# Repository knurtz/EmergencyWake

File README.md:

## Idea
A bedside alarm clock that uses a big red [emergency brake lever](https://www.google.com/search?tbm=isch&q=notbremse%20zug&tbs=imgo:1) as a snooze button.

To display the time, a vintage [VFD](https://en.wikipedia.org/wiki/Vacuum_fluorescent_display) is used.

An STM32 microcontroller and its RTC unit is used for tracking the time. It's in deep sleep most of the time.

Soundfiles from an SD card can be read by the microcontroller and played back through a small speaker.

Because of the VFD's relatively high power consumption, the clock can't run on battery power alone, so a USB-C connector is used for a 5 V power supply. 

In case of a power outage, a 3 V coin cell battery powers the microcontroller. In this scenario a small buzzer will be used instead of a wakeup melody, in order to use as little power as possible and to also notify the user, something's wrong. Also the display won't work.

Also, there will be support for a [DCF77](https://en.wikipedia.org/wiki/DCF77) radio clock module to automatically update the time.

A toggle switch allows programming two independent alarms. The times are set using a rotary encoder.

## Resources
- [Useful information](http://www.vwlowen.co.uk/arduino/vfd/vfd-clock.htm) about VFDs
- [A Guide to Fundamental VFD Operation](https://www.noritake-elec.com/technology/general-technical-information/vfd-operation)
- [Instructables page](https://www.instructables.com/id/A-Simple-Driver-for-VFD-Displays/) about controlling VFDs
- [Github project](https://github.com/AndruPol/ChibiOS-WavePlayer) about an STM32 wave player with ChibiOS
- [Github project](https://github.com/vanbwodonk/F4D_MP3) about an STM32 MP3 decoder
- [Another Github project](https://github.com/no111u3/stm32f4d_encoder/blob/master/main.c) about using the timer's encoder mode

## Components
- used emergency brake from eBay
- VFD from [pollin.de](https://www.pollin.de/p/vakuum-fluoreszenzdisplay-futaba-4-lt-46zb3-4-digit-121537) with additional parts:
  - [PT6312B](https://datasheet.lcsc.com/szlcsc/Princeton-Tech-PT6312B_C110225.pdf) VFD controller IC (requires negative voltages)
  - Alternative: UDN6118 VFD driver IC from eBay with no need for negative voltage
  - L9110 H-bridge for VFD filament
  - GL5516 light dependent resistor from eBay
- STM32F407VET6 microcontroller
- SD card holder from [Würth](https://www.we-online.de/katalog/datasheet/693071020811.pdf)
- DCF77 module from [pollin.de](https://www.pollin.de/p/dcf-empfangsmodul-dcf1-810054)
- CR2032 coin cell holder
- small buzzer
- toggle switch from [pollin.de](https://www.pollin.de/p/kippschalter-kn3-c-103a-1-polig-on-off-on-420023)
- rotary encoder from [reichelt.de](https://www.reichelt.de/drehimpulsegeber-15-impulse-30-rastungen-vertikal-stec11b03-p73913.html?r=1)
- MC34063 DCDC converter
- 5 V to 3.3 V step down regulator from [Würth](https://www.we-online.de/katalog/datasheet/173950378.pdf)
- [WM8960](https://datasheet.lcsc.com/szlcsc/Wolfson-Microelectronics-PLC-WM8960CGEFL-RV_C18752.pdf) audio codec with integrated class-D amplifier

## Usage
The clock will be in deep sleep most of the time. The display can be activated for about 10 seconds by tugging the emergency brake shortly.

While the time is being displayed, flipping the toggle switch into one of its two "on" positions allows setting the alarm times. In this mode, the alarms can each be (de-)activated by pulling the emergency lever once. A deactivated alarm will be represented by \_\_:\_\_ on the display.

Setting the alarm time is done by pressing the rotary encoder's push button to set the hours and then pressing it again to set the minutes. Alarm times are stored inside an EEPROM IC to avoid loss of settings after a power outage.

Once one alarm rings, pulling the emergency lever shortly will put it into snooze mode, pulling longer will deactivate the alarm.

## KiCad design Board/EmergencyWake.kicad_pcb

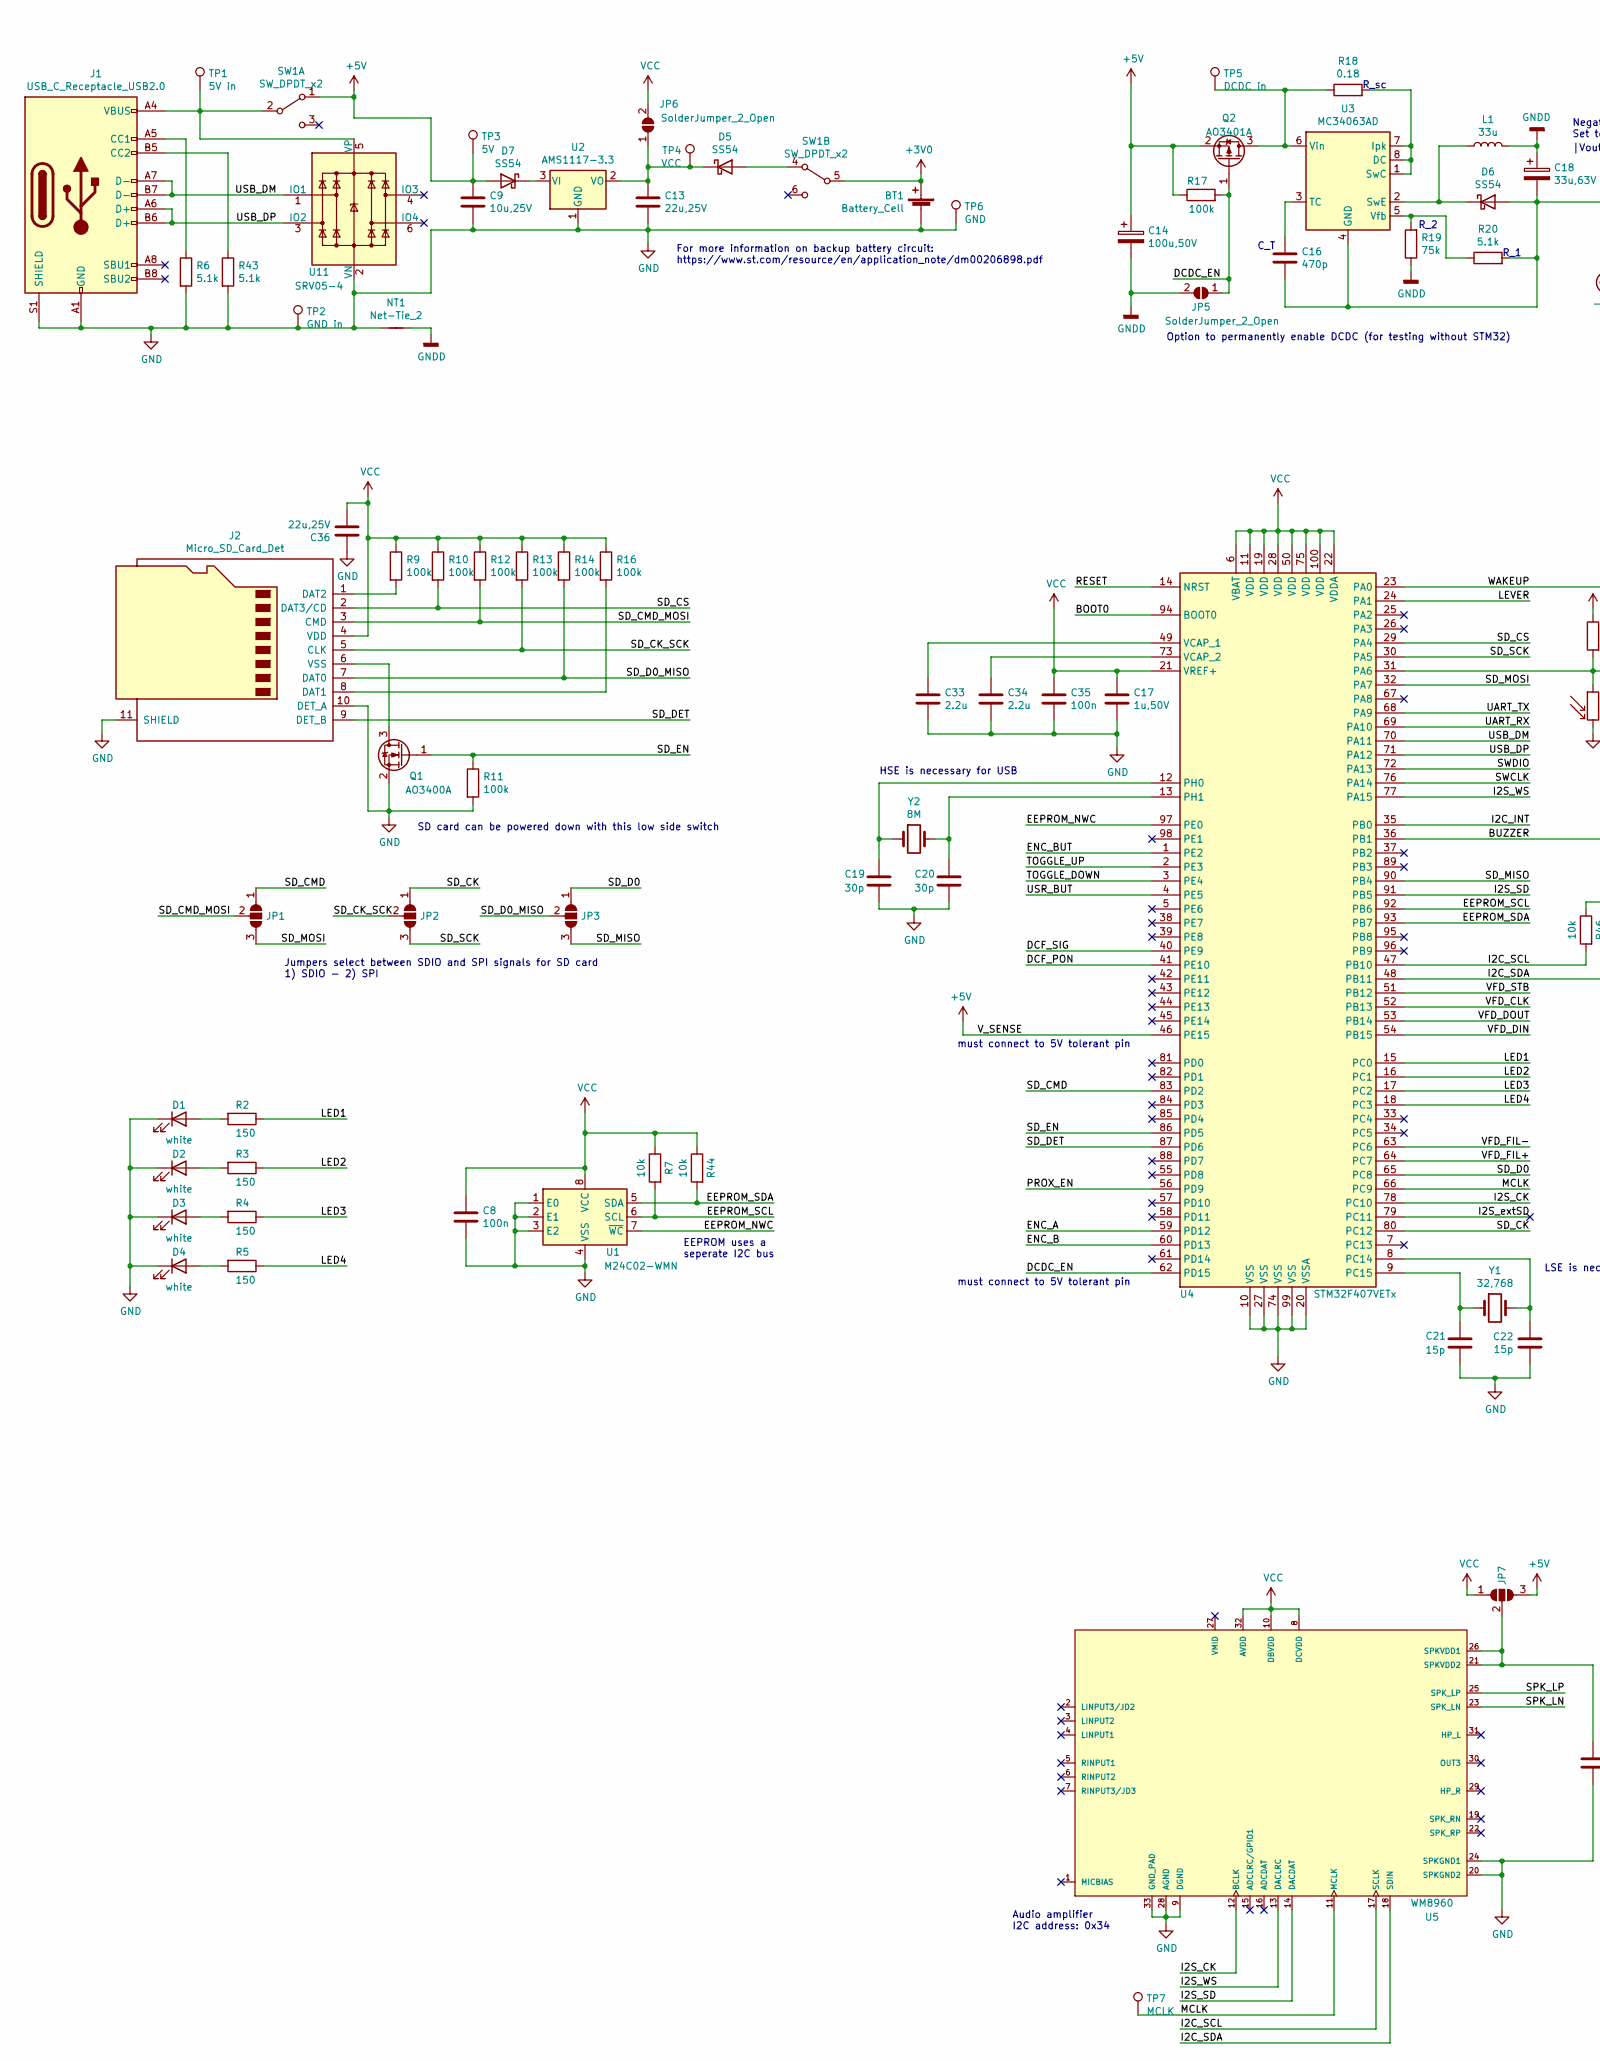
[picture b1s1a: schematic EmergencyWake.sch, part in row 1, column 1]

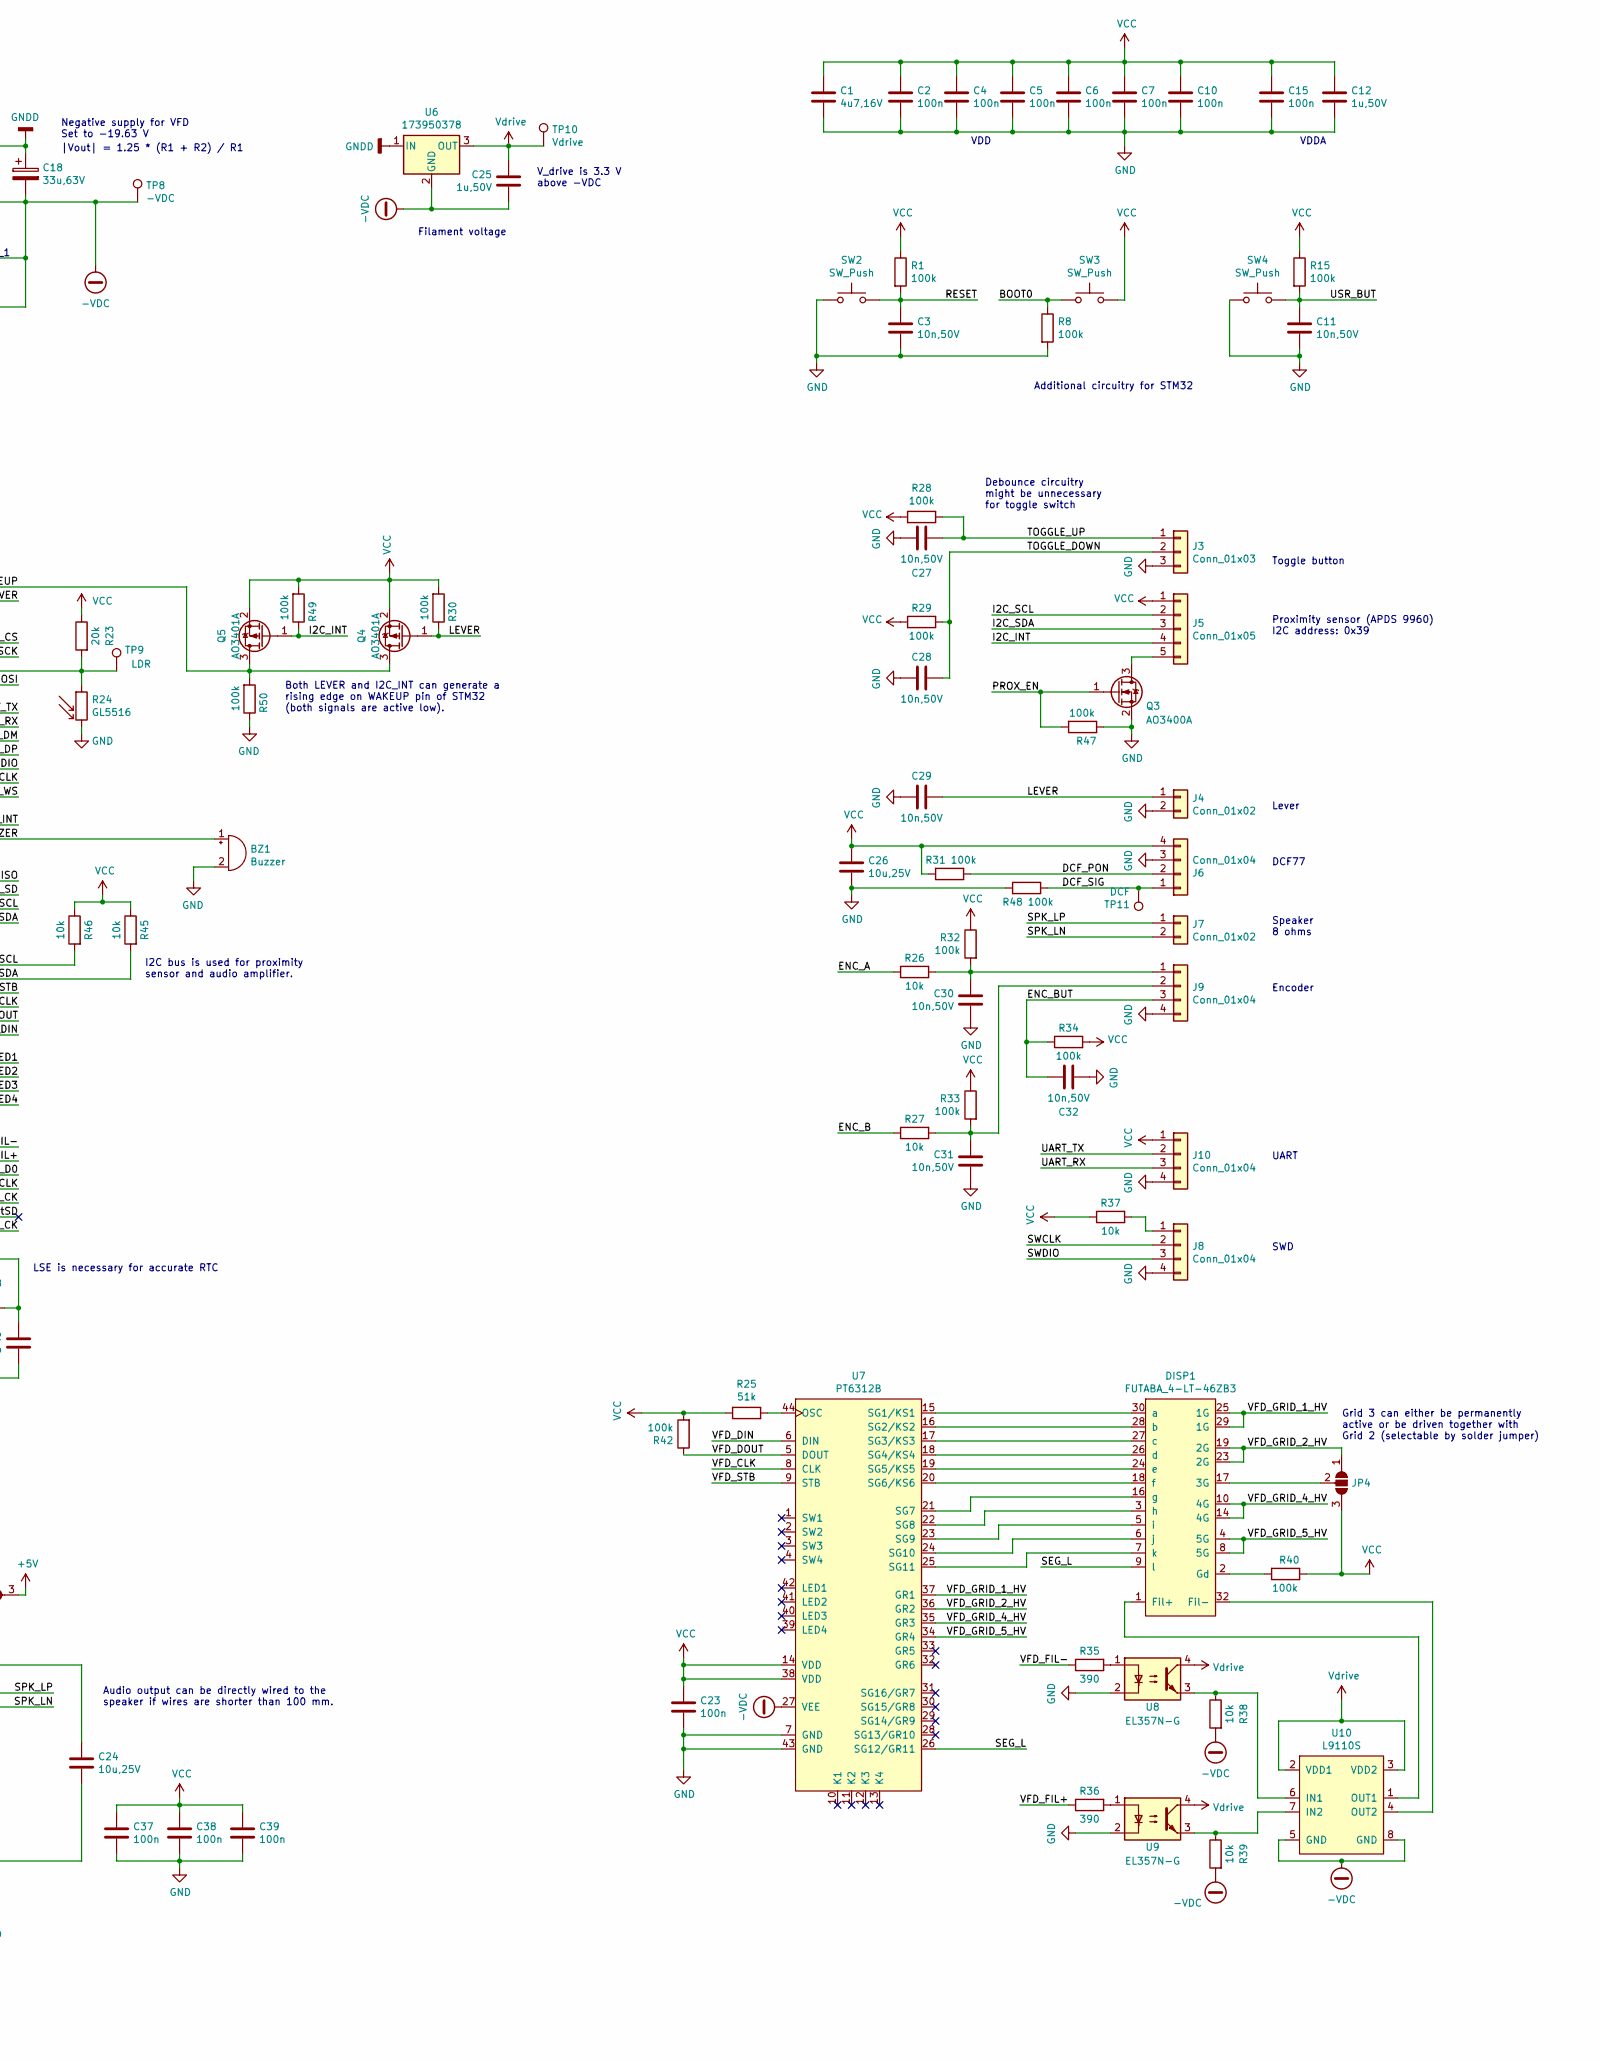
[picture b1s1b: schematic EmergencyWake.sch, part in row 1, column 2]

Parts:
BT1: Battery_Cell; 79523141
BZ1: Buzzer; Buzzer_12x9.5RM7.6
C1: 4u7,16V; C_0603_1608Metric; LCSC C19666
C2, C4, C5, C6, C7, C8, C10, C15, C23, C35, C37, C38, C39: 100n; C_0402_1005Metric; LCSC C1525
C3, C11, C27, C28, C29, C30, C31, C32: 10n,50V; C_0402_1005Metric; LCSC C15195
C9, C24, C26: 10u,25V; C_0805_2012Metric; LCSC C15850
C12, C17, C25: 1u,50V; C_0603_1608Metric; LCSC C15849
C13, C36: 22u,25V; C_0805_2012Metric; LCSC C45783
C14: 100u,50V; CP_Radial_D6.3mm_P2.50mm
C16: 470p; C_0603_1608Metric; LCSC C1620
C18: 33u,63V; CP_Radial_D6.3mm_P2.50mm
C19, C20: 30p; C_0402_1005Metric; LCSC C1570
C21, C22: 15p; C_0402_1005Metric; LCSC C1548
C33, C34: 2.2u; C_0603_1608Metric; LCSC C23630
D1, D2, D3, D4: white; LED_0805_2012Metric_Castellated; LCSC C34499
D5, D6, D7: SS54; D_SMA; LCSC C22452
DISP1: FUTABA_4-LT-46ZB3
J1: USB_C_Receptacle_USB2.0; 632723300011
J2: Micro_SD_Card_Det; 693071020811
J3: Conn_01x03; PinHeader_1x03_P2.54mm_Horizontal
J4, J7: Conn_01x02; PinHeader_1x02_P2.54mm_Horizontal
J5: Conn_01x05; PinHeader_1x05_P2.54mm_Horizontal
J6, J9: Conn_01x04; PinHeader_1x04_P2.54mm_Horizontal
J8, J10: Conn_01x04; WR-WTB 2.00mm SMT Male Horizontal Shrouded Header 4 Pins
JP1, JP2, JP3, JP4, JP7: SolderJumper_3_Open; SolderJumper-3_P1.3mm_Open_RoundedPad1.0x1.5mm_NumberLabels
JP5, JP6: SolderJumper_2_Open; SolderJumper-2_P1.3mm_Open_TrianglePad1.0x1.5mm
L1: 33u; L_Wuerth_WE-PD-Typ-7345
NT1: Net-Tie_2; NetTie-2_SMD_Pad2.0mm
Q1, Q3: AO3400A; SOT-23; LCSC C20917
Q2, Q4, Q5: AO3401A; SOT-23; LCSC C15127
R1, R8, R9, R10, R11, R12, R13, R14, R15, R16, R17, R28, R29, R30, R31, R32, R33, R34, R40, R42, R47, R48, R49, R50: 100k; R_0402_1005Metric; LCSC C25741
R2, R3, R4, R5: 150; R_0402_1005Metric; LCSC C25082
R6, R20, R43: 5.1k; R_0603_1608Metric; LCSC C23186
R7, R44, R45, R46: 10k; R_0402_1005Metric; LCSC C25804
R18: 0.18; 561070332057
R19: 75k; R_0603_1608Metric; LCSC C23242
R23: 20k; R_0603_1608Metric; LCSC C4184
R24: GL5516; R_LDR_5.1x4.3mm_P3.4mm_Vertical
R25: 51k; R_0603_1608Metric; LCSC C23196
R26, R27: 10k; R_0402_1005Metric; LCSC C25744
R35, R36: 390; R_0603_1608Metric; LCSC C23151
R37, R38, R39: 10k; R_0603_1608Metric; LCSC C25804
SW1: SW_DPDT_x2; 452404020202
SW2, SW3, SW4: SW_Push; 436351045816
TP1: 5V in; TestPoint_Loop_D1.80mm_Drill1.0mm_Beaded
TP2: GND in; TestPoint_Loop_D1.80mm_Drill1.0mm_Beaded
TP3: 5V; TestPoint_Loop_D1.80mm_Drill1.0mm_Beaded
TP4: VCC; TestPoint_Loop_D1.80mm_Drill1.0mm_Beaded
TP5: DCDC in; TestPoint_Loop_D1.80mm_Drill1.0mm_Beaded
TP6: GND; TestPoint_Loop_D1.80mm_Drill1.0mm_Beaded
TP7: MCLK; TestPoint_Loop_D1.80mm_Drill1.0mm_Beaded
TP8: -VDC; TestPoint_Loop_D1.80mm_Drill1.0mm_Beaded
TP9: LDR; TestPoint_Loop_D1.80mm_Drill1.0mm_Beaded
TP10: Vdrive; TestPoint_Loop_D1.80mm_Drill1.0mm_Beaded
TP11: DCF; TestPoint_Loop_D1.80mm_Drill1.0mm_Beaded
U1: M24C02-WMN; SOIC-8_3.9x4.9mm_P1.27mm; LCSC C7562
U2: AMS1117-3.3; SOT-223-3_TabPin2; LCSC C6186
U3: MC34063AD; SOIC-8_3.9x4.9mm_P1.27mm; LCSC C32078
U4: STM32F407VETx; LQFP-100_14x14mm_P0.5mm; LCSC C28730
U5: WM8960; QFN-32-1EP_5x5mm_P0.5mm_EP3.45x3.45mm; LCSC C18752
U6: 173950378; Converter_DCDC_RECOM_R-78B-2.0_THT
U7: PT6312B; LQFP-44_10x10mm_P0.8mm; LCSC C110225
U8, U9: EL357N-G; SOP-4_3.8x4.1mm_P2.54mm; LCSC C6649
U10: L9110S; SOP-8_3.76x4.96mm_P1.27mm; LCSC C85174
U11: SRV05-4; SOT-23-6; LCSC C85364
Y1: 32,768; Crystal_SMD_3215-2Pin_3.2x1.5mm; LCSC C32346
Y2: 8M; Crystal_SMD_5032-2Pin_5.0x3.2mm; LCSC C115962

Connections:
+3V0: BT1.1 (+), SW1.5 (B)
+5V: C9.1, C14.1, D7.2 (A), JP7.3 (B), Q2.2 (S), R17.1, SW1.1 (A), TP3.1, U4.46 (PE15)
-VDC: C16.2, C18.2, C25.2, D6.2 (A), R20.2, R38.2, R39.2, TP8.1, U3.4 (GND), U6.2 (GND), U7.27 (VEE), U10.5 (GND), U10.8 (GND)
/BOOT0: R8.1, SW3.1, U4.94 (BOOT0)
/BUZZER: BZ1.1 (-), U4.36 (PB1)
/DCDC_EN: JP5.1 (A), Q2.1 (G), R17.2, U4.62 (PD15)
/DCF_PON: J6.2, R31.1, U4.41 (PE10)
/DCF_SIG: J6.1, R48.1, TP11.1, U4.40 (PE9)
/EEPROM_NWC: U1.7 (~WC), U4.97 (PE0)
/EEPROM_SCL: R7.2, U1.6 (SCL), U4.92 (PB6)
/EEPROM_SDA: R44.2, U1.5 (SDA), U4.93 (PB7)
/ENC_A: R26.1, U4.59 (PD12)
/ENC_B: R27.1, U4.60 (PD13)
/ENC_BUT: C32.2, J9.3, R34.1, U4.1 (PE2)
/I2C_INT: J5.4, Q5.1 (G), R49.1, U4.35 (PB0)
/I2C_SCL: J5.2, R46.2, U4.47 (PB10), U5.17 (SCLK)
/I2C_SDA: J5.3, R45.2, U4.48 (PB11), U5.18 (SDIN)
/I2S_CK: U4.78 (PC10), U5.12 (BCLK)
/I2S_SD: U4.91 (PB5), U5.14 (DACDAT)
/I2S_WS: U4.77 (PA15), U5.13 (DACLRC)
/I2S_extSD: U4.79 (PC11)
/LED1: R2.1, U4.15 (PC0)
/LED2: R3.1, U4.16 (PC1)
/LED3: R4.1, U4.17 (PC2)
/LED4: R5.1, U4.18 (PC3)
/LEVER: C29.2, J4.1, Q4.1 (G), R30.1, U4.24 (PA1)
/MCLK: TP7.1, U4.66 (PC9), U5.11 (MCLK)
/PROX_EN: Q3.1 (G), R47.2, U4.56 (PD9)
/RESET: C3.1, R1.2, SW2.2, U4.14 (NRST)
/SD_CK: JP2.1 (A), U4.80 (PC12)
/SD_CK_SCK: J2.5 (CLK), JP2.2 (C), R13.2
/SD_CMD: JP1.1 (A), U4.83 (PD2)
/SD_CMD_MOSI: J2.3 (CMD), JP1.2 (C), R12.2
/SD_CS: J2.2 (DAT3/CD), R10.2, U4.29 (PA4)
/SD_D0: JP3.1 (A), U4.65 (PC8)
/SD_D0_MISO: J2.7 (DAT0), JP3.2 (C), R14.2
/SD_DET: J2.9 (DET_B), U4.87 (PD6)
/SD_EN: Q1.1 (G), R11.1, U4.86 (PD5)
/SD_MISO: JP3.3 (B), U4.90 (PB4)
/SD_MOSI: JP1.3 (B), U4.32 (PA7)
/SD_SCK: JP2.3 (B), U4.30 (PA5)
/SEG_L: DISP1.9 (l), U7.26 (SG12/GR11)
/SPK_LN: J7.2, U5.23 (SPK_LN)
/SPK_LP: J7.1, U5.25 (SPK_LP)
/SWCLK: J8.2, U4.76 (PA14)
/SWDIO: J8.3, U4.72 (PA13)
/TOGGLE_DOWN: C28.2, J3.2, R29.1, U4.3 (PE4)
/TOGGLE_UP: C27.2, J3.1, R28.1, U4.2 (PE3)
/UART_RX: J10.3, U4.69 (PA10)
/UART_TX: J10.2, U4.68 (PA9)
/USB_DM: J1.A7 (D-), J1.B7 (D-), U4.70 (PA11), U11.1 (IO1)
/USB_DP: J1.A6 (D+), J1.B6 (D+), U4.71 (PA12), U11.3 (IO2)
/USR_BUT: C11.1, R15.2, SW4.2, U4.4 (PE5)
/VFD_CLK: U4.52 (PB13), U7.8 (CLK)
/VFD_DIN: U4.54 (PB15), U7.6 (DIN)
/VFD_DOUT: R42.1, U4.53 (PB14), U7.5 (DOUT)
/VFD_FIL+: R36.1, U4.64 (PC7)
/VFD_FIL-: R35.1, U4.63 (PC6)
/VFD_GRID_1_HV: DISP1.25 (1G), DISP1.29 (1G), U7.37 (GR1)
/VFD_GRID_2_HV: DISP1.19 (2G), DISP1.23 (2G), JP4.1 (A), U7.36 (GR2)
/VFD_GRID_4_HV: DISP1.10 (4G), DISP1.14 (4G), U7.35 (GR3)
/VFD_GRID_5_HV: DISP1.4 (5G), DISP1.8 (5G), U7.34 (GR4)
/VFD_STB: U4.51 (PB12), U7.9 (STB)
/WAKEUP: Q4.3 (D), Q5.3 (D), R50.2, U4.23 (PA0)
GND: BT1.2 (-), BZ1.2 (+), C1.2, C2.2, C3.2, C4.2, C5.2, C6.2, C7.2, C8.2, C9.2, C10.2, C11.2, C12.2, C13.2, C15.2, C17.2, C19.2, C20.2, C21.2, C22.2, C23.2, C24.2, C26.2, C27.1, C28.1, C29.1, C30.2, C31.2, C32.1, C33.2, C34.2, C35.2, C36.1, C37.2, C38.2, C39.2, D1.1 (K), D2.1 (K), D3.1 (K), D4.1 (K), J1.A1 (GND), J1.A12 (GND), J1.B1 (GND), J1.B12 (GND), J1.S1 (SHIELD), J2.10 (DET_A), J2.11 (SHIELD), J3.3, J4.2, J6.3, J8.4, J9.4, J10.4, NT1.1, Q1.2 (S), Q3.2 (S), R6.2, R8.2, R11.2, R24.2, R43.2, R47.1, R48.2, R50.1, SW2.1, SW4.1, TP2.1, TP6.1, U1.1 (E0), U1.2 (E1), U1.3 (E2), U1.4 (VSS), U2.1 (GND), U4.10 (VSS), U4.20 (VSSA), U4.27 (VSS), U4.74 (VSS), U4.99 (VSS), U5.9 (DGND), U5.20 (SPKGND2), U5.24 (SPKGND1), U5.28 (AGND), U5.33 (GND_PAD), U7.7 (GND), U7.43 (GND), U8.2, U9.2, U11.2 (VN)
GNDD: C14.2, C18.1, JP5.2 (B), L1.2, NT1.2, R19.1, U6.1 (IN)
unnamed: C13.1, D5.1 (K), JP6.1 (A), TP4.1, U2.2 (VO)
unnamed: C16.1, U3.3 (TC)
unnamed: C19.1, U4.12 (PH0), Y2.1
unnamed: C20.1, U4.13 (PH1), Y2.2
unnamed: C21.1, U4.9 (PC15), Y1.1
unnamed: C22.1, U4.8 (PC14), Y1.2
unnamed: C24.1, JP7.2 (C), U5.21 (SPKVDD2), U5.26 (SPKVDD1)
unnamed: C30.1, J9.1, R26.2, R32.2
unnamed: C31.1, J9.2, R27.2, R33.2
unnamed: C33.1, U4.49 (VCAP_1)
unnamed: C34.1, U4.73 (VCAP_2)
unnamed: D1.2 (A), R2.2
unnamed: D2.2 (A), R3.2
unnamed: D3.2 (A), R4.2
unnamed: D4.2 (A), R5.2
unnamed: D5.2 (A), SW1.4 (A)
unnamed: D6.1 (K), L1.1, U3.2 (SwE)
unnamed: D7.1 (K), U2.3 (VI)
unnamed: DISP1.1 (Fil+), U10.1 (OUT1)
unnamed: DISP1.2 (Gd), R40.2
unnamed: DISP1.3 (h), U7.22 (SG8)
unnamed: DISP1.5 (i), U7.23 (SG9)
unnamed: DISP1.6 (j), U7.24 (SG10)
unnamed: DISP1.7 (k), U7.25 (SG11)
unnamed: DISP1.16 (g), U7.21 (SG7)
unnamed: DISP1.17 (3G), JP4.2 (C)
unnamed: DISP1.18 (f), U7.20 (SG6/KS6)
unnamed: DISP1.24 (e), U7.19 (SG5/KS5)
unnamed: DISP1.26 (d), U7.18 (SG4/KS4)
unnamed: DISP1.27 (c), U7.17 (SG3/KS3)
unnamed: DISP1.28 (b), U7.16 (SG2/KS2)
unnamed: DISP1.30 (a), U7.15 (SG1/KS1)
unnamed: DISP1.32 (Fil-), U10.4 (OUT2)
unnamed: J1.A4 (VBUS), J1.A9 (VBUS), J1.B4 (VBUS), J1.B9 (VBUS), SW1.2 (B), TP1.1, U11.5 (VP)
unnamed: J1.A5 (CC1), R6.1
unnamed: J1.B5 (CC2), R43.1
unnamed: J2.1 (DAT2), R9.2
unnamed: J2.6 (VSS), Q1.3 (D)
unnamed: J2.8 (DAT1), R16.2
unnamed: J5.5, Q3.3 (D)
unnamed: J8.1, R37.2
unnamed: Q2.3 (D), R18.1, TP5.1, U3.6 (Vin)
unnamed: R18.2, U3.1 (SwC), U3.7 (Ipk), U3.8 (DC)
unnamed: R19.2, R20.1, U3.5 (Vfb)
unnamed: R23.2, R24.1, TP9.1, U4.31 (PA6)
unnamed: R25.1, U7.44 (OSC)
unnamed: R35.2, U8.1
unnamed: R36.2, U9.1
unnamed: R38.1, U8.3, U10.6 (IN1)
unnamed: R39.1, U9.3, U10.7 (IN2)
VCC: C1.1, C2.1, C4.1, C5.1, C6.1, C7.1, C8.1, C10.1, C12.1, C15.1, C17.1, C23.1, C26.1, C35.1, C36.2, C37.1, C38.1, C39.1, J2.4 (VDD), J5.1, J6.4, J10.1, JP4.3 (B), JP6.2 (B), JP7.1 (A), Q4.2 (S), Q5.2 (S), R1.1, R7.1, R9.1, R10.1, R12.1, R13.1, R14.1, R15.1, R16.1, R23.1, R25.2, R28.2, R29.2, R30.2, R31.2, R32.1, R33.1, R34.2, R37.1, R40.1, R42.2, R44.1, R45.1, R46.1, R49.2, SW3.2, U1.8 (VCC), U4.6 (VBAT), U4.11 (VDD), U4.19 (VDD), U4.21 (VREF+), U4.22 (VDDA), U4.28 (VDD), U4.50 (VDD), U4.75 (VDD), U4.100 (VDD), U5.8 (DCVDD), U5.10 (DBVDD), U5.32 (AVDD), U7.14 (VDD), U7.38 (VDD)
Vdrive: C25.1, TP10.1, U6.3 (OUT), U8.4, U9.4, U10.2 (VDD1), U10.3 (VDD2)

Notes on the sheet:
SWD
Speaker 8 ohms
DCF77
Toggle button
Lever
Encoder
must connect to 5V tolerant pin
For more information on backup battery circuit: https://www.st.com/resource/en/application_note/dm00206898.pdf
Debounce circuitry might be unnecessary for toggle switch
Grid 3 can either be permanently active or be driven together with Grid 2 (selectable by solder jumper)
Negative supply for VFD Set to -19.63 V
R_1
C_T
R_sc
|Vout| = 1.25 * (R1 + R2) / R1
VDD
VDDA
R_2
V_drive is 3.3 V above -VDC
Proximity sensor (APDS 9960) I2C address: 0x39
UART
Both LEVER and I2C_INT can generate a rising edge on WAKEUP pin of STM32 (both signals are active low).
I2C bus is used for proximity sensor and audio amplifier.
HSE is necessary for USB
LSE is necessary for accurate RTC
EEPROM uses a seperate I2C bus
Jumpers select between SDIO and SPI signals for SD card 1) SDIO - 2) SPI
SD card can be powered down with this low side switch
Option to permanently enable DCDC (for testing without STM32)
Filament voltage
Additional circuitry for STM32
Audio amplifier I2C address: 0x34
Audio output can be directly wired to the speaker if wires are shorter than 100 mm.

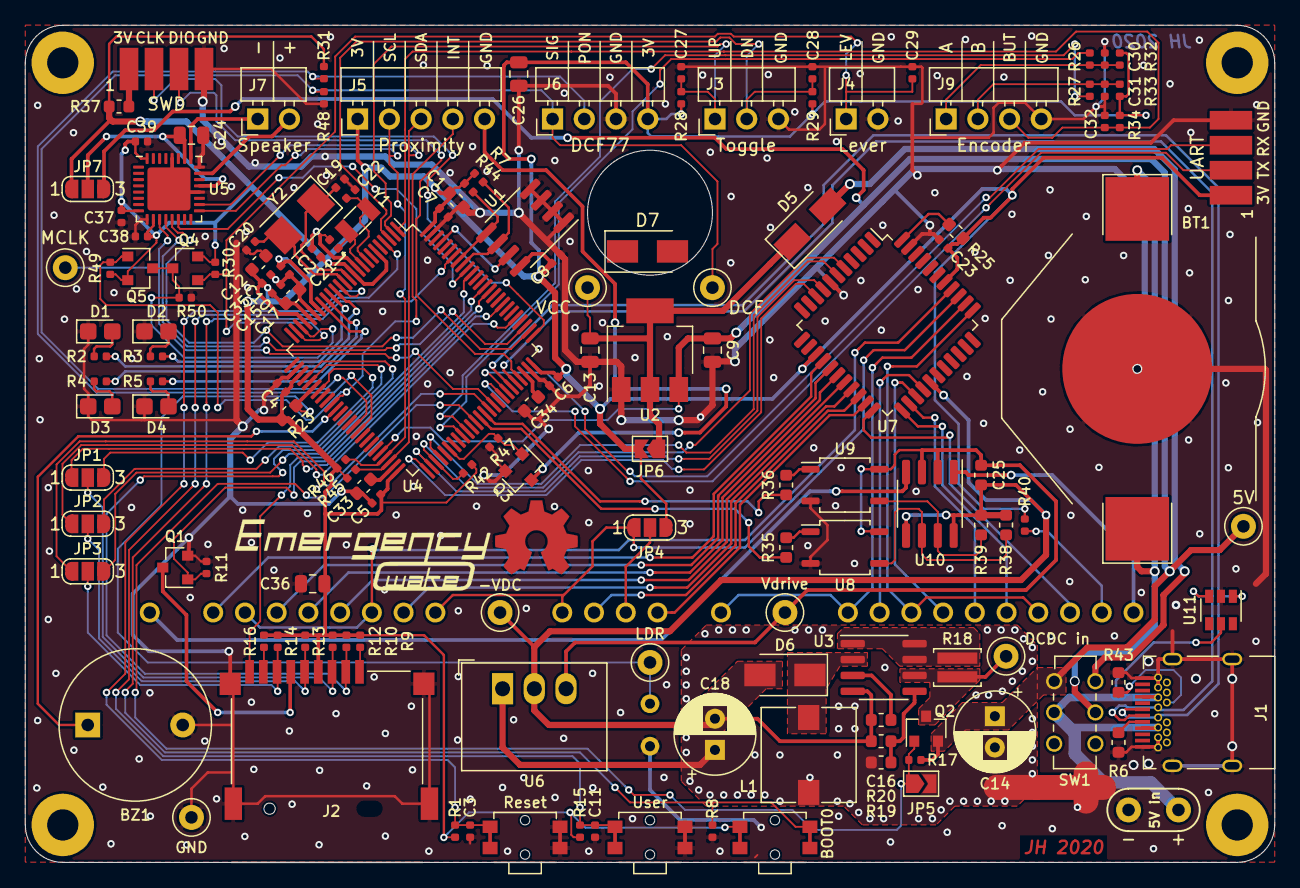
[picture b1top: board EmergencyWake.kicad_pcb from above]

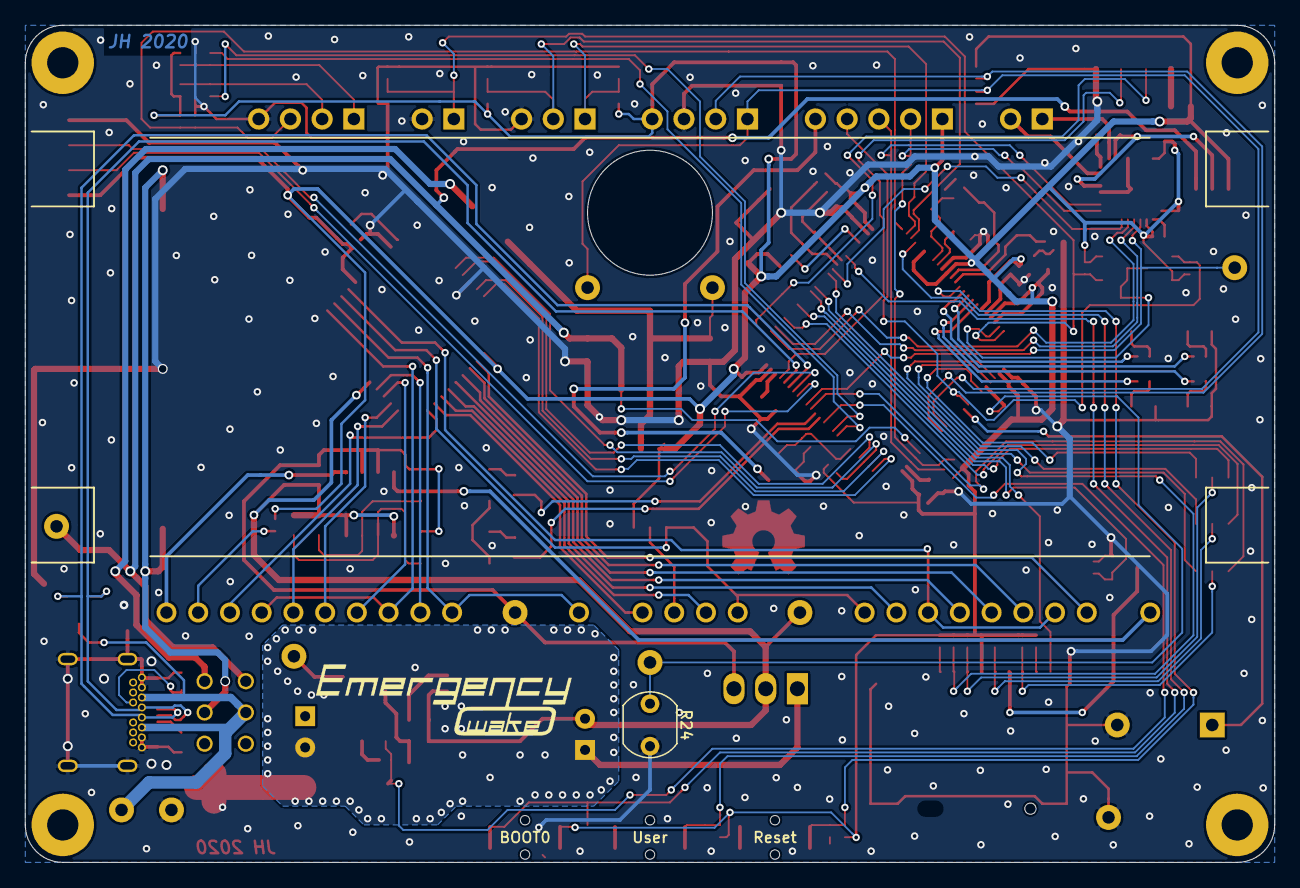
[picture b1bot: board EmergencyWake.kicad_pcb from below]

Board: 2 copper layers, 100.0 x 67.0 mm, 148 parts (2 on the bottom side), 117 nets.

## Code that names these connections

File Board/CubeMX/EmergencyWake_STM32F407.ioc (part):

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Mcu.Name=STM32F407V(E-G)Tx
Mcu.Package=LQFP100
Mcu.UserName=STM32F407VETx
PA0-WKUP.Mode=SYS_WakeUp0
PA0-WKUP.Signal=SYS_WKUP
PA1.GPIOParameters=GPIO_Label
PA1.GPIO_Label=Lever
PA1.Signal=GPXTI1
PA10.Mode=Asynchronous
PA10.Signal=USART1_RX
PA11.Mode=Device_Only
PA11.Signal=USB_OTG_FS_DM
PA12.Mode=Device_Only
PA12.Signal=USB_OTG_FS_DP
PA13.Mode=Serial_Wire
PA13.Signal=SYS_JTMS-SWDIO
PA14.Mode=Serial_Wire
PA14.Signal=SYS_JTCK-SWCLK
PA15.Mode=Full_Duplex_Master
PA15.Signal=I2S3_WS
PA4.Mode=NSS_Signal_Hard_Output
PA4.Signal=SPI1_NSS
PA5.Mode=Full_Duplex_Master
PA5.Signal=SPI1_SCK
PA6.GPIOParameters=GPIO_Label
PA6.GPIO_Label=LDR in
PA6.Signal=ADCx_IN6
PA7.Mode=Full_Duplex_Master
PA7.Signal=SPI1_MOSI
PA9.Mode=Asynchronous
PA9.Signal=USART1_TX
PB0.GPIOParameters=GPIO_Label
PB0.GPIO_Label=I2C_INT
PB0.Signal=GPXTI0
PB1.GPIOParameters=GPIO_Label
PB1.GPIO_Label=Buzzer
PB1.Signal=GPIO_Output
PB10.Mode=I2C
PB10.Signal=I2C2_SCL
PB11.Mode=I2C
PB11.Signal=I2C2_SDA
PB12.GPIOParameters=GPIO_Label
PB12.GPIO_Label=SPI2_STB
PB12.Signal=GPIO_Output
PB13.Mode=Full_Duplex_Master
PB13.Signal=SPI2_SCK
PB14.Mode=Full_Duplex_Master
PB14.Signal=SPI2_MISO
PB15.Mode=Full_Duplex_Master
PB15.Signal=SPI2_MOSI
PB4.Mode=Full_Duplex_Master
PB4.Signal=SPI1_MISO
PB5.Mode=Full_Duplex_Master
PB5.Signal=I2S3_SD
PB6.Mode=I2C
PB6.Signal=I2C1_SCL
PB7.Mode=I2C
PB7.Signal=I2C1_SDA
PC0.GPIOParameters=GPIO_Label
PC0.GPIO_Label=LED1
PC0.Signal=GPIO_Output
PC1.GPIOParameters=GPIO_Label
PC1.GPIO_Label=LED2
PC1.Signal=GPIO_Output
PC10.Mode=Full_Duplex_Master
PC10.Signal=I2S3_CK
PC11.Mode=Full_Duplex_Master
PC11.Signal=I2S3_ext_SD
PC12.Mode=SD_1_bit
PC12.Signal=SDIO_CK
PC14-OSC32_IN.Mode=LSE-External-Oscillator
PC14-OSC32_IN.Signal=RCC_OSC32_IN
PC15-OSC32_OUT.Mode=LSE-External-Oscillator
PC15-OSC32_OUT.Signal=RCC_OSC32_OUT
PC2.GPIOParameters=GPIO_Label
PC2.GPIO_Label=LED3
PC2.Signal=GPIO_Output
PC3.GPIOParameters=GPIO_Label
PC3.GPIO_Label=LED4
PC3.Signal=GPIO_Output
PC6.Signal=S_TIM8_CH1
PC7.Signal=S_TIM8_CH2
PC8.Mode=SD_1_bit
PC8.Signal=SDIO_D0
PC9.Mode=Clock-out-2
PC9.Signal=RCC_MCO_2
PD12.Signal=S_TIM4_CH1
PD13.Signal=S_TIM4_CH2
PD15.GPIOParameters=GPIO_Label
PD15.GPIO_Label=DCDC enable
PD15.Signal=GPIO_Output
PD2.Mode=SD_1_bit
PD2.Signal=SDIO_CMD
PD5.GPIOParameters=GPIO_Label
PD5.GPIO_Label=SD enable
PD5.Signal=GPIO_Output
PD6.GPIOParameters=GPIO_Label
PD6.GPIO_Label=SD detect
PD6.Signal=GPIO_Input
PD9.GPIOParameters=GPIO_Label
PD9.GPIO_Label=I2C2_EN
PD9.Signal=GPIO_Output
PE0.GPIOParameters=GPIO_Label
PE0.GPIO_Label=EEPROM_NWC
PE0.Signal=GPIO_Output
PE10.GPIOParameters=GPIO_Label
PE10.GPIO_Label=DCF77 enable
PE10.Signal=GPIO_Output
PE15.GPIOParameters=GPIO_Label
PE15.GPIO_Label=VBUS sense
PE15.Signal=GPIO_Input
PE2.GPIOParameters=GPIO_Label
PE2.GPIO_Label=EncoderButton
PE2.Signal=GPXTI2
PE3.GPIOParameters=GPIO_Label
PE3.GPIO_Label=ToggleUp
PE3.Signal=GPXTI3
PE4.GPIOParameters=GPIO_Label
PE4.GPIO_Label=ToggleDown
PE4.Signal=GPXTI4
PE5.GPIOParameters=GPIO_Label
PE5.GPIO_Label=USR_BUT
PE5.Signal=GPXTI5
PE9.GPIOParameters=GPIO_Label
PE9.GPIO_Label=DCF77 signal
PE9.Signal=S_TIM1_CH1
PH0-OSC_IN.Mode=HSE-External-Oscillator
PH0-OSC_IN.Signal=RCC_OSC_IN
PH1-OSC_OUT.Mode=HSE-External-Oscillator
PH1-OSC_OUT.Signal=RCC_OSC_OUT
RCC.HSE_VALUE=8000000
RCC.SYSCLKFreq_VALUE=72000000
RCC.SYSCLKSource=RCC_SYSCLKSOURCE_PLLCLK
board=custom

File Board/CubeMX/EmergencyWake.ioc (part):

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Mcu.Name=STM32F103V(C-D-E)Tx
Mcu.Package=LQFP100
Mcu.UserName=STM32F103VETx
PA0-WKUP.Mode=SYS_WakeUp0
PA0-WKUP.Signal=SYS_WKUP
PA1.GPIOParameters=GPIO_Label
PA1.GPIO_Label=Lever
PA1.Signal=GPXTI1
PA10.Mode=Asynchronous
PA10.Signal=USART1_RX
PA11.Mode=Device
PA11.Signal=USB_DM
PA12.Mode=Device
PA12.Signal=USB_DP
PA13.Mode=Serial_Wire
PA13.Signal=SYS_JTMS-SWDIO
PA14.Mode=Serial_Wire
PA14.Signal=SYS_JTCK-SWCLK
PA15.Mode=NSS_Signal_Hard_Input
PA15.Signal=SPI1_NSS
PA3.GPIOParameters=GPIO_Label
PA3.GPIO_Label=Audio EN
PA3.Signal=GPIO_Output
PA4.GPIOParameters=GPIO_Label
PA4.GPIO_Label=Audio out
PA4.Signal=COMP_DAC1_group
PA6.GPIOParameters=GPIO_Label
PA6.GPIO_Label=LDR in
PA6.Signal=ADCx_IN6
PA9.Mode=Asynchronous
PA9.Signal=USART1_TX
PB1.GPIOParameters=GPIO_Label
PB1.GPIO_Label=Buzzer
PB1.Signal=GPIO_Output
PB12.GPIOParameters=GPIO_Label
PB12.GPIO_Label=SPI2_STB
PB12.Signal=GPIO_Output
PB13.Mode=Full_Duplex_Master
PB13.Signal=SPI2_SCK
PB14.Mode=Full_Duplex_Master
PB14.Signal=SPI2_MISO
PB15.Mode=Full_Duplex_Master
PB15.Signal=SPI2_MOSI
PB3.Mode=Full_Duplex_Master
PB3.Signal=SPI1_SCK
PB4.Mode=Full_Duplex_Master
PB4.Signal=SPI1_MISO
PB5.Mode=Full_Duplex_Master
PB5.Signal=SPI1_MOSI
PB6.Mode=I2C
PB6.Signal=I2C1_SCL
PB7.Mode=I2C
PB7.Signal=I2C1_SDA
PC0.GPIOParameters=GPIO_Label
PC0.GPIO_Label=LED1
PC0.Signal=GPIO_Output
PC1.GPIOParameters=GPIO_Label
PC1.GPIO_Label=LED2
PC1.Signal=GPIO_Output
PC12.Mode=SD_1_bit
PC12.Signal=SDIO_CK
PC14-OSC32_IN.Mode=LSE-External-Oscillator
PC14-OSC32_IN.Signal=RCC_OSC32_IN
PC15-OSC32_OUT.Mode=LSE-External-Oscillator
PC15-OSC32_OUT.Signal=RCC_OSC32_OUT
PC2.GPIOParameters=GPIO_Label
PC2.GPIO_Label=LED3
PC2.Signal=GPIO_Output
PC3.GPIOParameters=GPIO_Label
PC3.GPIO_Label=LED4
PC3.Signal=GPIO_Output
PC6.Signal=S_TIM8_CH1
PC7.Signal=S_TIM8_CH2
PC8.Mode=SD_1_bit
PC8.Signal=SDIO_D0
PD12.Signal=S_TIM4_CH1
PD13.Signal=S_TIM4_CH2
PD15.GPIOParameters=GPIO_Label
PD15.GPIO_Label=DCDC enable
PD15.Signal=GPIO_Output
PD2.Mode=SD_1_bit
PD2.Signal=SDIO_CMD
PD5.GPIOParameters=GPIO_Label
PD5.GPIO_Label=SD enable
PD5.Signal=GPIO_Output
PD6.GPIOParameters=GPIO_Label
PD6.GPIO_Label=SD detect
PD6.Signal=GPIO_Input
PE0.GPIOParameters=GPIO_Label
PE0.GPIO_Label=EEPROM_NWC
PE0.Signal=GPIO_Output
PE10.GPIOParameters=GPIO_Label
PE10.GPIO_Label=DCF77 enable
PE10.Signal=GPIO_Output
PE15.GPIOParameters=GPIO_Label
PE15.GPIO_Label=VBUS sense
PE15.Signal=GPIO_Input
PE2.GPIOParameters=GPIO_Label
PE2.GPIO_Label=EncoderButton
PE2.Signal=GPXTI2
PE3.GPIOParameters=GPIO_Label
PE3.GPIO_Label=ToggleUp
PE3.Signal=GPXTI3
PE4.GPIOParameters=GPIO_Label
PE4.GPIO_Label=ToggleDown
PE4.Signal=GPXTI4
PE5.GPIOParameters=GPIO_Label
PE5.GPIO_Label=USR_BUT
PE5.Signal=GPXTI5
PE9.GPIOParameters=GPIO_Label
PE9.GPIO_Label=DCF77 signal
PE9.Signal=S_TIM1_CH1
board=custom

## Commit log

2020-01-19 [Initial commit] Folder strucure, Datasheet, CubeMX files
2020-01-19 [Board] Renamed CubeMX file
2020-01-19 Added readme
2020-01-19 Fixed typos in readme
2020-01-20 Link to DCF77
2020-01-20 [Readme] New toggle switch, link to encoder, typos
2020-01-20 [Readme] Link to timer in encoder mode
2020-01-21 [Readme] Added guide to VFD operation
2020-01-21 [Readme] Changed for new VFD IC with more features
2020-01-21 [Readme] Added instructables
2020-01-23 [Readme] Changed driver IC once again
2020-01-23 [Board] Started layout with mechanically fixed components
2020-01-23 [Board] Added a lot of main components
2020-01-24 [Board] Added a lot more components to schematic
2020-01-24 [Documents] Added STM32 datasheet, added PDF extension for manual
2020-01-25 [Board] Added IC and wiring for VFD
2020-01-25 [Documents] Added datasheet for VFD IC UDN6118
2020-01-25 [Board] Added motor driver for VFD filament
2020-01-27 [Board] Added all remaining components, arranged them approximately on PCB
2020-01-29 [Board] Switched some pins in CubeMX
2020-01-31 [Board] Changed VFD driver, added DC/DC converter for -24V
2020-02-01 [Board] Some tweaks on the schematic
2020-02-01 [Board] Wired all signals to STM32
2020-02-01 [Board] Cleaned up schematic sections
2020-02-02 [Board] Switched some pins around
2020-02-02 [Board] Placed a lot of components!
2020-02-03 [Board] Placed most components, only TPs missing
2020-02-05 [Board] Changed lever to active high, replaced LDO for filament
2020-02-05 [Board] Moved all components to the front of the board
2020-02-05 [Board] Finished moving components to front of board
2020-02-06 [Board] Checked schematic for errors
2020-02-09 [Images] Added Emergency Wake Logo
2020-02-09 [Board] Added logo and changed USB plug type
2020-02-09 [Board] Added GNDD and routed DCDC converter
2020-02-10 [Readme] Added logo
2020-02-10 [Readme] Documented recent changes in the design.
2020-02-10 [Board] Rearranged DCDC converter
2020-02-11 [Board] Cleaned up silkscreen
2020-02-12 [Libs] New footprints and 3D models for Würth components
2020-02-12 [Board] Changed SD and battery holder to Würth components
2020-02-12 [Board] Cleanup before changing MCU once again
2020-02-12 [Documents] Added datasheet and manual for F4
2020-02-12 [Board] Switched from F103 to F407
2020-02-13 [Board] Cleand up silk screen
2020-02-13 [Board] Did some routing
2020-02-14 [Readme] Some new information
2020-02-14 [Board] Removed solder paste for not-fitted components. Added I2C for proximity sensor. Moved SWD and UART connector
2020-02-14 [Board] More routing done
2020-02-16 [Board] More routing
2020-02-16 [Code] Copied example project for STM32F4 discovery
2020-02-17 [Board] Routed USB, UART and buttons
2020-02-19 [Board] Added TVS diodes for USB
2020-02-19 [Board] Routing done, cleanup necessary
2020-02-19 [Board] Routing cleaned up, GND vias missing
2020-02-20 [Board] Fixed some errors
2020-02-20 [Board] Added stitching vias
2020-02-20 [Board] Some last changes to the layout
2020-02-20 [Board] Generated bills of material for each vendor
2020-02-20 [Board] Added positions file
2020-02-21 [Code] Added config file for VS Code project
2020-02-21 [Code] Modified board specific files for new project
2020-02-21 [Code] Changed clock settings
2020-02-21 [Board] First version of Gerber files
2020-02-21 [Code] Removed license text in main from default project
2020-02-22 [Code] Modified example project to use USB serial - not working
2020-02-22 [Code] Narrowed down the USB problem
2020-02-22 [Code] Setting higher system speed solved USB problem
2020-02-22 [Code] Fixed USB by correctly initializing pins
2020-02-22 [Code] USB says Hello World
2020-02-22 [Code] Shell works
2020-02-24 [Code] Copied SDC test, doesn't work yet
2020-02-24 [Documents] Added STM32F4 discovery manual
2020-02-25 [Board] Added OR gate for wakeup signal
2020-03-03 [Board] New fabrication files
2020-03-04 [Board] Corrected assembly information for JLCPCB
2020-03-06 [Board] Some minor changes
2020-03-07 [Board] Final changes for order
2020-03-18 [Documents] Datasheet for alternative DAC with integrated amp
2020-03-21 [Documents] Datasheet for proximity sensor
2020-03-22 [Board] Replaced audio amplifier
2020-03-23 [Board] Cleaned up GND fill around STM32
2020-03-23 [Board] Minor tweaks, switched position of 5V input and USB protection diodes
2020-03-25 [Board] Minor Layout changes
2020-03-25 [Board] New assembly information after changing audio amp
2020-03-26 [Board] Results of DFM analysis at JLCPCB
2020-03-26 [Readme] Updated info on audio amp
2020-04-03 [Board] SDC example finally works, updated clocks in CubeMX project to make ChibiOS happy
2020-04-03 [Code] Removed bulk of SD card tests
2020-04-03 [Code] Copied SD card FatFS example code.
2020-04-03 [Code] Missing config file
2020-04-04 [Code] Updated pin definitions, tested MCO2
2020-04-04 [Code] Added I2C
2020-04-04 [Code] Reading proximity values works
2020-04-08 [Code] Designed basic statemachine layout
2020-04-09 [Code] Added function to compare systime
2020-04-14 [Readme] Removed old audio amp, added MP3 project
2020-04-19 [Code] A lot of work on statemachine and general program execution workflow
2020-04-22 [Code] Ported code to use custom board instead of discovery
2020-04-22 [Code] Re-enabled SD card functions to test new board
2020-04-23 [Code] Added code for audio output. Does not work yet
2020-04-24 [Code] Fixed static noise, I2S still in wrong state
2020-04-24 [Code] Audio output works
2020-04-24 [CubeMX] Save to new version of program
2020-04-24 [Code] Fixed I2S frequencies
2020-04-25 [Code] Playing wave file from SD card works
2020-04-26 [Documents] Added display driver datasheet
2020-04-27 [Code] Implemented display driver. Still buggy
2020-04-28 [Code] Changed SPI to LSB first
2020-04-28 [Code] Tested display, added small animation
2020-04-28 [Code] Some helper functions to display data.
2020-04-29 [Code] Buzzer and encoder work now
2020-04-30 [Code] Optimized switch case for 7-segment numbers
2020-05-02 [Code] Introduced device status. Added global events and external interrupts
2020-05-05 [Code] More work on events
2020-05-20 [Code] Changes to event system
2020-05-31 [Code] Cleaned up events in main and some changes to statemachine handler
2020-06-20 [Board] Added diode in front of LDO, exported STEP filefor CAD
2020-06-21 [BrassPlates] Added Design ideas for etched brass plates
2020-06-21 [Brass Plates] Modified design and exported for vinyl cutter and CAD
2020-06-21 [CAD] Added construction for Autodesk Inventor 2020
2020-07-02 [CAD] Some changes to the wooden backplate and brass plates
2020-08-11 [Code] Simpler config file for VSCode C/C++ extension
2020-08-11 [Code] Modification for new development environment under Windows
2020-08-11 [Code] Cleand up main.c
2020-08-12 [Code] Switched hex to bin number
2020-08-13 [Code] Some work on cleaning up statemachine handler
2020-08-19 [Code] Reworked statemachine a little bit.
2020-08-19 [Code] Made it compile
2020-08-23 [Code] Major rework of existing code (split into new files).
2020-08-24 [CAD] Increased pre-tension on spring
2020-08-24 [Code] compiles again
